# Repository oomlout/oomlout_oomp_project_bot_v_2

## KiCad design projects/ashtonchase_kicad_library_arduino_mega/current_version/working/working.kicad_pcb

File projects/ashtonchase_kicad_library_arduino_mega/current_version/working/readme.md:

# kicad_library
 
## summary 
* id: ashtonchase_kicad_library_arduino_mega
* user: ashtonchase
* name: kicad_library
* board: arduino_mega
* repo: https://github.com/ashtonchase/kicad-library
* src_file_repo_kicad_pcb: template/Arduino_Mega_R3/Arduino_Mega.kicad_pcb
* src_file_repo_kicad_pcb_link: https://github.com/ashtonchase/kicad-library/tree/master/template/Arduino_Mega_R3/Arduino_Mega.kicad_pcb

* src_file_repo_sch: template/Arduino_Mega_R3/Arduino_Mega.sch
* src_file_repo_sch_link: https://github.com/ashtonchase/kicad-library/tree/master/template/Arduino_Mega_R3/Arduino_Mega.sch
* full details link: https://github.com/oomlout/oomlout_oomp_project_bot_v_2/tree/main/projects/ashtonchase_kicad_library_arduino_mega/current_version/working  

## schematic  
  
[schematic (pdf)](working_schematic.pdf) 

## pcb  

[board (pdf)](working.pdf)  

## working_bom
| Id | Designator | Footprint | Quantity | Designation | Supplier and ref |  | None | 
| --- | --- | --- | --- | --- | --- | --- | --- | 
| 1 | P1 | Socket_Strip_Arduino_2x18 | 1 | Digital |  |  | [''] | 
| 2 | P2 | Socket_Strip_Arduino_1x08 | 1 | Power |  |  | [''] | 
| 3 | P3,P4 | Socket_Strip_Arduino_1x08 | 2 | Analog |  |  | [''] | 
| 4 | P5 | Socket_Strip_Arduino_1x10 | 1 | PWM |  |  | [''] | 
| 5 | P6 | Socket_Strip_Arduino_1x08 | 1 | PWM |  |  | [''] | 
| 6 | P7 | Socket_Strip_Arduino_1x08 | 1 | Communication |  |  | [''] | 
| 7 | P8,P9,P10,P11,P12,P13 | Arduino_1pin | 6 | CONN_01X01 |  |  | [''] | 

## bom_schematic
| Ref | Qnty | Value | Cmp name | Footprint | Description | Vendor | DNP | 
| --- | --- | --- | --- | --- | --- | --- | --- | 
| P1 | 1 | Digital | CONN_02X18 | Socket_Arduino_Mega:Socket_Strip_Arduino_2x18 |  |  |  | 
| P2 | 1 | Power | CONN_01X08 | Socket_Arduino_Mega:Socket_Strip_Arduino_1x08 |  |  |  | 
| P3, P4 | 2 | Analog | CONN_01X08 | Socket_Arduino_Mega:Socket_Strip_Arduino_1x08 |  |  |  | 
| P5 | 1 | PWM | CONN_01X10 | Socket_Arduino_Mega:Socket_Strip_Arduino_1x10 |  |  |  | 
| P6 | 1 | PWM | CONN_01X08 | Socket_Arduino_Mega:Socket_Strip_Arduino_1x08 |  |  |  | 
| P7 | 1 | Communication | CONN_01X08 | Socket_Arduino_Mega:Socket_Strip_Arduino_1x08 |  |  |  | 
| P8, P9, P10, P11, P12, P13 | 6 | CONN_01X01 | CONN_01X01 | Socket_Arduino_Mega:Arduino_1pin |  |  |  |

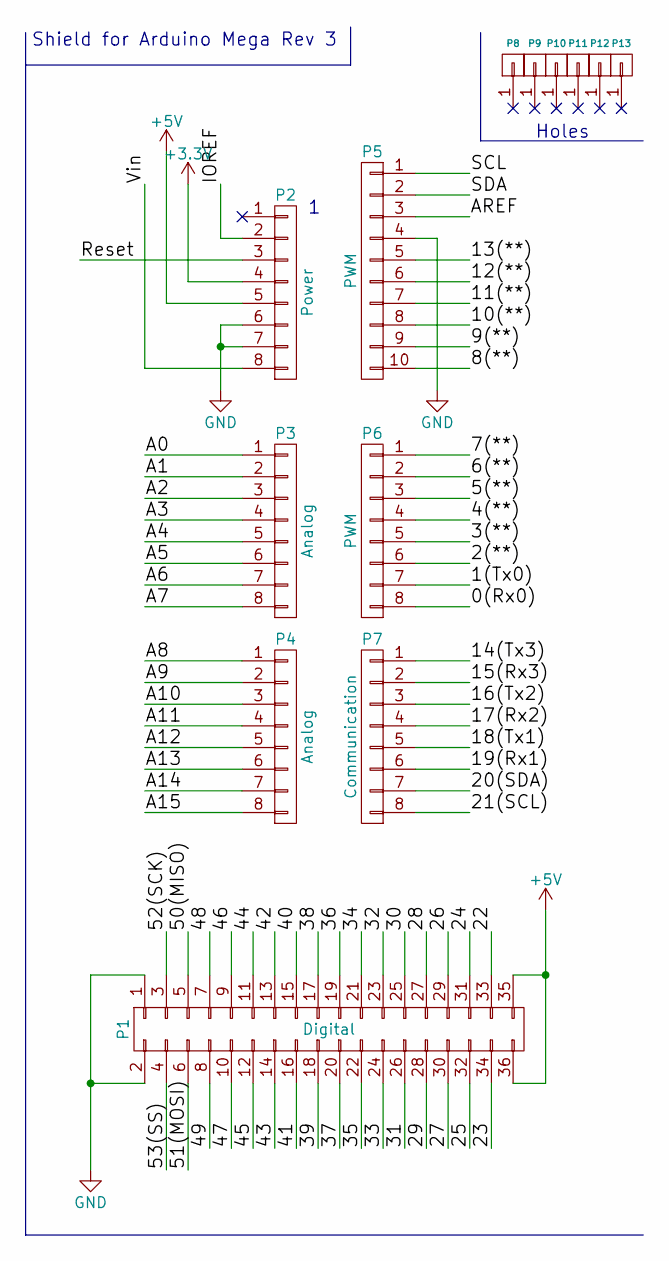
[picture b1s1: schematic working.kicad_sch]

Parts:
P1: Digital; Socket_Strip_Arduino_2x18
P2: Power; Socket_Strip_Arduino_1x08
P3, P4: Analog; Socket_Strip_Arduino_1x08
P5: PWM; Socket_Strip_Arduino_1x10
P6: PWM; Socket_Strip_Arduino_1x08
P7: Communication; Socket_Strip_Arduino_1x08
P8, P9, P10, P11, P12, P13: CONN_01X01; Arduino_1pin

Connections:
+3V3: P2.4
+5V: P1.35, P1.36, P2.5
/0(Rx0): P6.8
/1(Tx0): P6.7
/2(**): P6.6
/3(**): P6.5
/4(**): P6.4
/5(**): P6.3
/6(**): P6.2
/7(**): P6.1
/8(**): P5.10
/9(**): P5.9
/10(**): P5.8
/11(**): P5.7
/12(**): P5.6
/13(**): P5.5
/14(Tx3): P7.1
/15(Rx3): P7.2
/16(Tx2): P7.3
/17(Rx2): P7.4
/18(Tx1): P7.5
/19(Rx1): P7.6
/20(SDA): P7.7
/21(SCL): P7.8
/22: P1.33
/23: P1.34
/24: P1.31
/25: P1.32
/26: P1.29
/27: P1.30
/28: P1.27
/29: P1.28
/30: P1.25
/31: P1.26
/32: P1.23
/33: P1.24
/34: P1.21
/35: P1.22
/36: P1.19
/37: P1.20
/38: P1.17
/39: P1.18
/40: P1.15
/41: P1.16
/42: P1.13
/43: P1.14
/44: P1.11
/45: P1.12
/46: P1.9
/47: P1.10
/48: P1.7
/49: P1.8
/50(MISO): P1.5
/51(MOSI): P1.6
/52(SCK): P1.3
/53(SS): P1.4
/A0: P3.1
/A1: P3.2
/A2: P3.3
/A3: P3.4
/A4: P3.5
/A5: P3.6
/A6: P3.7
/A7: P3.8
/A8: P4.1
/A9: P4.2
/A10: P4.3
/A11: P4.4
/A12: P4.5
/A13: P4.6
/A14: P4.7
/A15: P4.8
/AREF: P5.3
/IOREF: P2.2
/Reset: P2.3
/SCL: P5.1
/SDA: P5.2
/Vin: P2.8
GND: P1.1, P1.2, P2.6, P2.7, P5.4

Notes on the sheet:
Holes
Shield for Arduino Mega Rev 3

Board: 2 copper layers, 13 parts (0 on the bottom side), 2 nets, no tracks yet.

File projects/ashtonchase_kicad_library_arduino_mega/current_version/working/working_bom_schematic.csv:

"Source:","C:\gh\oomlout_oomp_project_bot_v_2\projects\ashtonchase_kicad_library_arduino_mega\current_version\working\working.kicad_sch"
"Date:","25/09/2023 02:56:55"
"Tool:","Eeschema 7.0.6"
"Generator:","C:/Program Files/KiCad/7.0/bin/scripting/plugins/bom_csv_grouped_by_value_with_fp.py"
"Component Count:","13"
"Ref","Qnty","Value","Cmp name","Footprint","Description","Vendor","DNP"
"P1","1","Digital","CONN_02X18","Socket_Arduino_Mega:Socket_Strip_Arduino_2x18","","",""
"P2","1","Power","CONN_01X08","Socket_Arduino_Mega:Socket_Strip_Arduino_1x08","","",""
"P3, P4","2","Analog","CONN_01X08","Socket_Arduino_Mega:Socket_Strip_Arduino_1x08","","",""
"P5","1","PWM","CONN_01X10","Socket_Arduino_Mega:Socket_Strip_Arduino_1x10","","",""
"P6","1","PWM","CONN_01X08","Socket_Arduino_Mega:Socket_Strip_Arduino_1x08","","",""
"P7","1","Communication","CONN_01X08","Socket_Arduino_Mega:Socket_Strip_Arduino_1x08","","",""
"P8, P9, P10, P11, P12, P13","6","CONN_01X01","CONN_01X01","Socket_Arduino_Mega:Arduino_1pin","","",""

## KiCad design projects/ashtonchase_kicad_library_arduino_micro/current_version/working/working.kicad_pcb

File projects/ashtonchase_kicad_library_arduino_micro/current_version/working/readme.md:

# kicad_library
 
## summary 
* id: ashtonchase_kicad_library_arduino_micro
* user: ashtonchase
* name: kicad_library
* board: arduino_micro
* repo: https://github.com/ashtonchase/kicad-library
* src_file_repo_kicad_pcb: template/Arduino_Micro/Arduino_Micro.kicad_pcb
* src_file_repo_kicad_pcb_link: https://github.com/ashtonchase/kicad-library/tree/master/template/Arduino_Micro/Arduino_Micro.kicad_pcb

* src_file_repo_sch: template/Arduino_Micro/Arduino_Micro.sch
* src_file_repo_sch_link: https://github.com/ashtonchase/kicad-library/tree/master/template/Arduino_Micro/Arduino_Micro.sch
* full details link: https://github.com/oomlout/oomlout_oomp_project_bot_v_2/tree/main/projects/ashtonchase_kicad_library_arduino_micro/current_version/working  

## schematic  
  
[schematic (pdf)](working_schematic.pdf) 

## pcb  

[board (pdf)](working.pdf)  

## working_bom
| Id | Designator | Footprint | Quantity | Designation | Supplier and ref |  | None | 
| --- | --- | --- | --- | --- | --- | --- | --- | 
| 1 | P1 | Socket_Strip_Arduino_1x17 | 1 | Digital |  |  | [''] | 
| 2 | P2 | Socket_Strip_Arduino_1x17 | 1 | Analog |  |  | [''] | 
| 3 | P3,P4,P5,P6 | 1pin_Micro | 4 | CONN_01X01 |  |  | [''] | 

## bom_schematic
| Ref | Qnty | Value | Cmp name | Footprint | Description | Vendor | DNP | 
| --- | --- | --- | --- | --- | --- | --- | --- | 
| P1 | 1 | Digital | CONN_01X17 | Socket_Arduino_Micro:Socket_Strip_Arduino_1x17 |  |  |  | 
| P2 | 1 | Analog | CONN_01X17 | Socket_Arduino_Micro:Socket_Strip_Arduino_1x17 |  |  |  | 
| P3, P4, P5, P6 | 4 | CONN_01X01 | CONN_01X01 | Socket_Arduino_Micro:1pin_Micro |  |  |  |

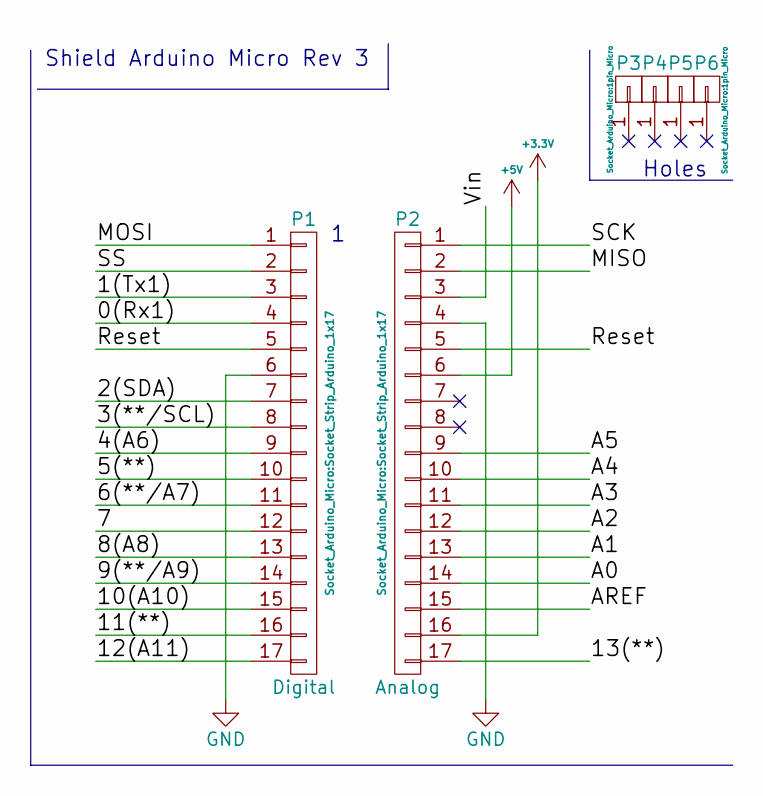
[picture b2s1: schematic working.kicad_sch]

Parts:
P1: Digital; Socket_Strip_Arduino_1x17
P2: Analog; Socket_Strip_Arduino_1x17
P3, P4, P5, P6: CONN_01X01; 1pin_Micro

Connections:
+3V3: P2.16
+5V: P2.6
/0(Rx1): P1.4
/1(Tx1): P1.3
/2(SDA): P1.7
/3(**/SCL): P1.8
/4(A6): P1.9
/5(**): P1.10
/6(**/A7): P1.11
/7: P1.12
/8(A8): P1.13
/9(**/A9): P1.14
/10(A10): P1.15
/11(**): P1.16
/12(A11): P1.17
/13(**): P2.17
/A0: P2.14
/A1: P2.13
/A2: P2.12
/A3: P2.11
/A4: P2.10
/A5: P2.9
/AREF: P2.15
/MISO: P2.2
/MOSI: P1.1
/Reset: P1.5, P2.5
/SCK: P2.1
/SS: P1.2
/Vin: P2.3
GND: P1.6, P2.4

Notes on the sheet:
Shield Arduino Micro Rev 3
Holes

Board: 2 copper layers, 6 parts (0 on the bottom side), 2 nets, no tracks yet.

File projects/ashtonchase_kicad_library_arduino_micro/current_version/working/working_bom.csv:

"Id";"Designator";"Footprint";"Quantity";"Designation";"Supplier and ref";
1;"P1";"Socket_Strip_Arduino_1x17";1;"Digital";;;
2;"P2";"Socket_Strip_Arduino_1x17";1;"Analog";;;
3;"P3,P4,P5,P6";"1pin_Micro";4;"CONN_01X01";;;

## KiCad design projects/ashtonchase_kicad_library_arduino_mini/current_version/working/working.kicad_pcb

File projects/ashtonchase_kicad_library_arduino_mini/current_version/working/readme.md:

# kicad_library
 
## summary 
* id: ashtonchase_kicad_library_arduino_mini
* user: ashtonchase
* name: kicad_library
* board: arduino_mini
* repo: https://github.com/ashtonchase/kicad-library
* src_file_repo_kicad_pcb: template/Arduino_Mini/Arduino_Mini.kicad_pcb
* src_file_repo_kicad_pcb_link: https://github.com/ashtonchase/kicad-library/tree/master/template/Arduino_Mini/Arduino_Mini.kicad_pcb

* src_file_repo_sch: template/Arduino_Mini/Arduino_Mini.sch
* src_file_repo_sch_link: https://github.com/ashtonchase/kicad-library/tree/master/template/Arduino_Mini/Arduino_Mini.sch
* full details link: https://github.com/oomlout/oomlout_oomp_project_bot_v_2/tree/main/projects/ashtonchase_kicad_library_arduino_mini/current_version/working  

## schematic  
  
[schematic (pdf)](working_schematic.pdf) 

## pcb  

[board (pdf)](working.pdf)  

## working_bom
| Id | Designator | Footprint | Quantity | Designation | Supplier and ref |  | None | 
| --- | --- | --- | --- | --- | --- | --- | --- | 
| 1 | P2 | Socket_Strip_Arduino_1x12 | 1 | Digital |  |  | [''] | 
| 2 | P4 | Socket_Strip_Arduino_1x05 | 1 | COM |  |  | [''] | 
| 3 | P5 | Socket_Strip_Arduino_1x12 | 1 | Analog |  |  | [''] | 
| 4 | P1,P3 | Socket_Strip_Arduino_1x02 | 2 | ADC |  |  | [''] | 
| 5 | P6 | Socket_Strip_Arduino_1x02 | 1 | PWR |  |  | [''] | 

## bom_schematic
| Ref | Qnty | Value | Cmp name | Footprint | Description | Vendor | DNP | 
| --- | --- | --- | --- | --- | --- | --- | --- | 
| P1, P3 | 2 | ADC | CONN_01X02 | Socket_Arduino_Mini:Socket_Strip_Arduino_1x02 |  |  |  | 
| P2 | 1 | Digital | CONN_01X12 | Socket_Arduino_Mini:Socket_Strip_Arduino_1x12 |  |  |  | 
| P4 | 1 | COM | CONN_01X05 | Socket_Arduino_Mini:Socket_Strip_Arduino_1x05 |  |  |  | 
| P5 | 1 | Analog | CONN_01X12 | Socket_Arduino_Mini:Socket_Strip_Arduino_1x12 |  |  |  | 
| P6 | 1 | PWR | CONN_01X02 | Socket_Arduino_Mini:Socket_Strip_Arduino_1x02 |  |  |  |

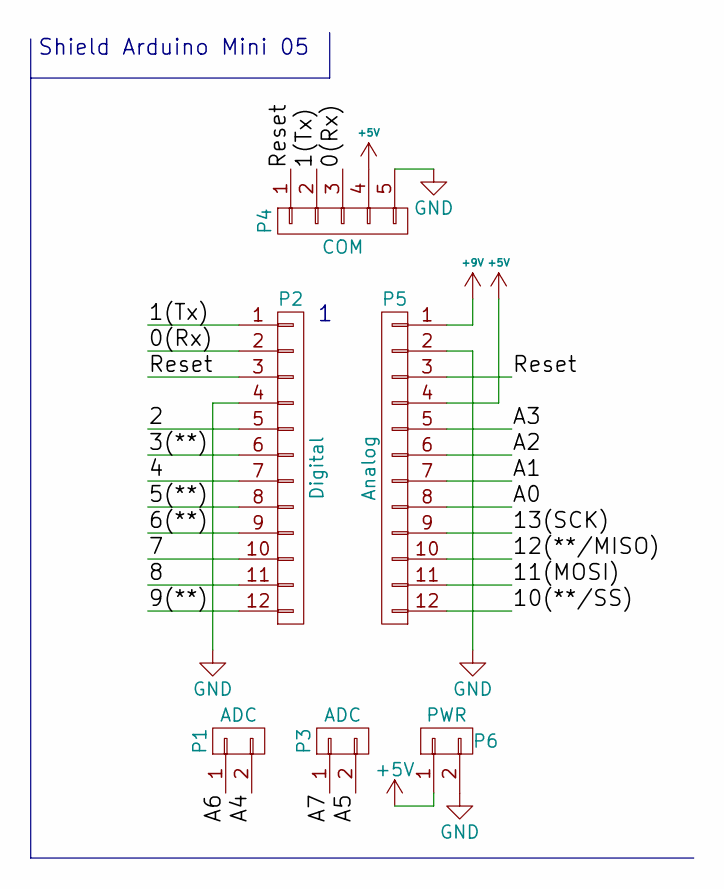
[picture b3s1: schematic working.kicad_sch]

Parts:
P1, P3: ADC; Socket_Strip_Arduino_1x02
P2: Digital; Socket_Strip_Arduino_1x12
P4: COM; Socket_Strip_Arduino_1x05
P5: Analog; Socket_Strip_Arduino_1x12
P6: PWR; Socket_Strip_Arduino_1x02

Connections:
+5V: P4.4, P5.4, P6.1
+9V: P5.1
/0(Rx): P2.2, P4.3
/1(Tx): P2.1, P4.2
/2: P2.5
/3(**): P2.6
/4: P2.7
/5(**): P2.8
/6(**): P2.9
/7: P2.10
/8: P2.11
/9(**): P2.12
/10(**/SS): P5.12
/11(MOSI): P5.11
/12(**/MISO): P5.10
/13(SCK): P5.9
/A0: P5.8
/A1: P5.7
/A2: P5.6
/A3: P5.5
/A4: P1.2
/A5: P3.2
/A6: P1.1
/A7: P3.1
/Reset: P2.3, P4.1, P5.3
GND: P2.4, P4.5, P5.2, P6.2

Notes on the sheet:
Shield Arduino Mini 05

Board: 2 copper layers, 6 parts (0 on the bottom side), 5 nets, no tracks yet.

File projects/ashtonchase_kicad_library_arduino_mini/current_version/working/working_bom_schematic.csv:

"Source:","C:\gh\oomlout_oomp_project_bot_v_2\projects\ashtonchase_kicad_library_arduino_mini\current_version\working\working.kicad_sch"
"Date:","25/09/2023 03:12:44"
"Tool:","Eeschema 7.0.6"
"Generator:","C:/Program Files/KiCad/7.0/bin/scripting/plugins/bom_csv_grouped_by_value_with_fp.py"
"Component Count:","6"
"Ref","Qnty","Value","Cmp name","Footprint","Description","Vendor","DNP"
"P1, P3","2","ADC","CONN_01X02","Socket_Arduino_Mini:Socket_Strip_Arduino_1x02","","",""
"P2","1","Digital","CONN_01X12","Socket_Arduino_Mini:Socket_Strip_Arduino_1x12","","",""
"P4","1","COM","CONN_01X05","Socket_Arduino_Mini:Socket_Strip_Arduino_1x05","","",""
"P5","1","Analog","CONN_01X12","Socket_Arduino_Mini:Socket_Strip_Arduino_1x12","","",""
"P6","1","PWR","CONN_01X02","Socket_Arduino_Mini:Socket_Strip_Arduino_1x02","","",""

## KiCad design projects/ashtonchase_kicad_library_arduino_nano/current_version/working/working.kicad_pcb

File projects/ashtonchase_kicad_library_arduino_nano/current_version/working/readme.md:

# kicad_library
 
## summary 
* id: ashtonchase_kicad_library_arduino_nano
* user: ashtonchase
* name: kicad_library
* board: arduino_nano
* repo: https://github.com/ashtonchase/kicad-library
* src_file_repo_kicad_pcb: template/Arduino_Nano/Arduino_Nano.kicad_pcb
* src_file_repo_kicad_pcb_link: https://github.com/ashtonchase/kicad-library/tree/master/template/Arduino_Nano/Arduino_Nano.kicad_pcb

* src_file_repo_sch: template/Arduino_Nano/Arduino_Nano.sch
* src_file_repo_sch_link: https://github.com/ashtonchase/kicad-library/tree/master/template/Arduino_Nano/Arduino_Nano.sch
* full details link: https://github.com/oomlout/oomlout_oomp_project_bot_v_2/tree/main/projects/ashtonchase_kicad_library_arduino_nano/current_version/working  

## schematic  
  
[schematic (pdf)](working_schematic.pdf) 

## pcb  

[board (pdf)](working.pdf)  

## working_bom
| Id | Designator | Footprint | Quantity | Designation | Supplier and ref |  | None | 
| --- | --- | --- | --- | --- | --- | --- | --- | 
| 1 | P1 | Socket_Strip_Arduino_1x15 | 1 | Digital |  |  | [''] | 
| 2 | P2 | Socket_Strip_Arduino_1x15 | 1 | Analog |  |  | [''] | 
| 3 | P3,P4,P5,P6 | 1pin_Nano | 4 | CONN_01X01 |  |  | [''] | 

## bom_schematic
| Ref | Qnty | Value | Cmp name | Footprint | Description | Vendor | DNP | 
| --- | --- | --- | --- | --- | --- | --- | --- | 
| P1 | 1 | Digital | CONN_01X15 | Socket_Arduino_Nano:Socket_Strip_Arduino_1x15 |  |  |  | 
| P2 | 1 | Analog | CONN_01X15 | Socket_Arduino_Nano:Socket_Strip_Arduino_1x15 |  |  |  | 
| P3, P4, P5, P6 | 4 | CONN_01X01 | CONN_01X01 | Socket_Arduino_Nano:1pin_Nano |  |  |  |

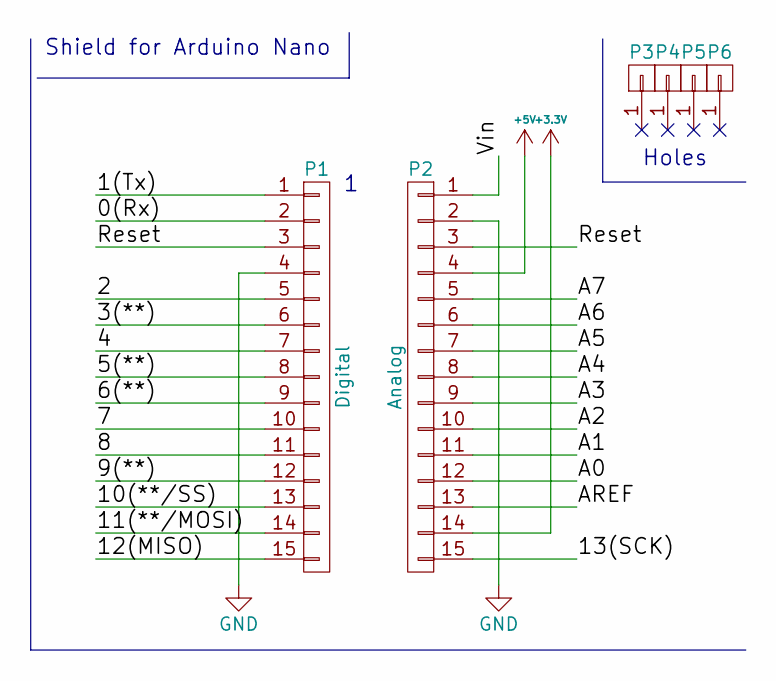
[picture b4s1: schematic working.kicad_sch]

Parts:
P1: Digital; Socket_Strip_Arduino_1x15
P2: Analog; Socket_Strip_Arduino_1x15
P3, P4, P5, P6: CONN_01X01; 1pin_Nano

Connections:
+3V3: P2.14
+5V: P2.4
/0(Rx): P1.2
/1(Tx): P1.1
/2: P1.5
/3(**): P1.6
/4: P1.7
/5(**): P1.8
/6(**): P1.9
/7: P1.10
/8: P1.11
/9(**): P1.12
/10(**/SS): P1.13
/11(**/MOSI): P1.14
/12(MISO): P1.15
/13(SCK): P2.15
/A0: P2.12
/A1: P2.11
/A2: P2.10
/A3: P2.9
/A4: P2.8
/A5: P2.7
/A6: P2.6
/A7: P2.5
/AREF: P2.13
/Reset: P1.3, P2.3
/Vin: P2.1
GND: P1.4, P2.2

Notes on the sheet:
Shield for Arduino Nano
Holes

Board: 2 copper layers, 6 parts (0 on the bottom side), 2 nets, no tracks yet.

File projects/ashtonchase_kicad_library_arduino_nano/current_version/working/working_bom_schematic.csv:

"Source:","C:\gh\oomlout_oomp_project_bot_v_2\projects\ashtonchase_kicad_library_arduino_nano\current_version\working\working.kicad_sch"
"Date:","25/09/2023 03:20:39"
"Tool:","Eeschema 7.0.6"
"Generator:","C:/Program Files/KiCad/7.0/bin/scripting/plugins/bom_csv_grouped_by_value_with_fp.py"
"Component Count:","6"
"Ref","Qnty","Value","Cmp name","Footprint","Description","Vendor","DNP"
"P1","1","Digital","CONN_01X15","Socket_Arduino_Nano:Socket_Strip_Arduino_1x15","","",""
"P2","1","Analog","CONN_01X15","Socket_Arduino_Nano:Socket_Strip_Arduino_1x15","","",""
"P3, P4, P5, P6","4","CONN_01X01","CONN_01X01","Socket_Arduino_Nano:1pin_Nano","","",""

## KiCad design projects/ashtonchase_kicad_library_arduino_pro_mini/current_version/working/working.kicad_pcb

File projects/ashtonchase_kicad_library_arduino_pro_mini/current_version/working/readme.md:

# kicad_library
 
## summary 
* id: ashtonchase_kicad_library_arduino_pro_mini
* user: ashtonchase
* name: kicad_library
* board: arduino_pro_mini
* repo: https://github.com/ashtonchase/kicad-library
* src_file_repo_kicad_pcb: template/Arduino_Pro_Mini/Arduino_Pro_Mini.kicad_pcb
* src_file_repo_kicad_pcb_link: https://github.com/ashtonchase/kicad-library/tree/master/template/Arduino_Pro_Mini/Arduino_Pro_Mini.kicad_pcb

* src_file_repo_sch: template/Arduino_Pro_Mini/Arduino_Pro_Mini.sch
* src_file_repo_sch_link: https://github.com/ashtonchase/kicad-library/tree/master/template/Arduino_Pro_Mini/Arduino_Pro_Mini.sch
* full details link: https://github.com/oomlout/oomlout_oomp_project_bot_v_2/tree/main/projects/ashtonchase_kicad_library_arduino_pro_mini/current_version/working  

## schematic  
  
[schematic (pdf)](working_schematic.pdf) 

## pcb  

[board (pdf)](working.pdf)  

## working_bom
| Id | Designator | Footprint | Quantity | Designation | Supplier and ref |  | None | 
| --- | --- | --- | --- | --- | --- | --- | --- | 
| 1 | P1 | Socket_Strip_Arduino_1x12 | 1 | Digital |  |  | [''] | 
| 2 | P2 | Socket_Strip_Arduino_1x06 | 1 | COM |  |  | [''] | 
| 3 | P3,P5 | Socket_Strip_Arduino_1x02 | 2 | ADC |  |  | [''] | 
| 4 | P4 | Socket_Strip_Arduino_1x12 | 1 | Analog |  |  | [''] | 

## bom_schematic
| Ref | Qnty | Value | Cmp name | Footprint | Description | Vendor | DNP | 
| --- | --- | --- | --- | --- | --- | --- | --- | 
| P1 | 1 | Digital | CONN_01X12 | Socket_Arduino_Pro_Mini:Socket_Strip_Arduino_1x12 |  |  |  | 
| P2 | 1 | COM | CONN_01X06 | Socket_Arduino_Pro_Mini:Socket_Strip_Arduino_1x06 |  |  |  | 
| P3, P5 | 2 | ADC | CONN_01X02 | Socket_Arduino_Pro_Mini:Socket_Strip_Arduino_1x02 |  |  |  | 
| P4 | 1 | Analog | CONN_01X12 | Socket_Arduino_Pro_Mini:Socket_Strip_Arduino_1x12 |  |  |  |

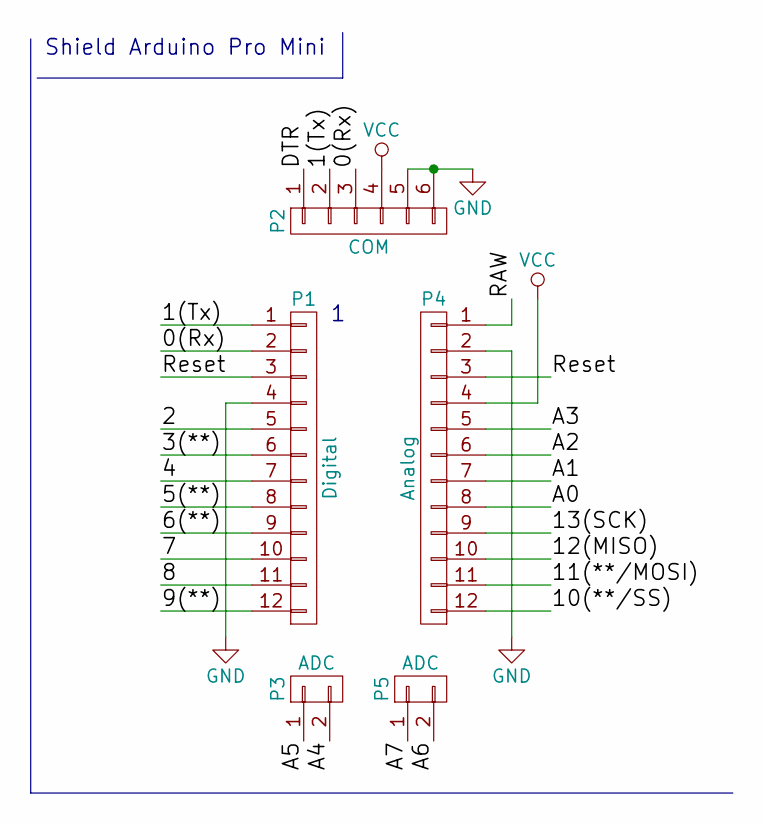
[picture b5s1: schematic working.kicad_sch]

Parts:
P1: Digital; Socket_Strip_Arduino_1x12
P2: COM; Socket_Strip_Arduino_1x06
P3, P5: ADC; Socket_Strip_Arduino_1x02
P4: Analog; Socket_Strip_Arduino_1x12

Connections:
/0(Rx): P1.2, P2.3
/1(Tx): P1.1, P2.2
/2: P1.5
/3(**): P1.6
/4: P1.7
/5(**): P1.8
/6(**): P1.9
/7: P1.10
/8: P1.11
/9(**): P1.12
/10(**/SS): P4.12
/11(**/MOSI): P4.11
/12(MISO): P4.10
/13(SCK): P4.9
/A0: P4.8
/A1: P4.7
/A2: P4.6
/A3: P4.5
/A4: P3.2
/A5: P3.1
/A6: P5.2
/A7: P5.1
/DTR: P2.1
/RAW: P4.1
/Reset: P1.3, P4.3
GND: P1.4, P2.5, P2.6, P4.2
VCC: P2.4, P4.4

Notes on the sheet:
Shield Arduino Pro Mini

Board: 2 copper layers, 5 parts (0 on the bottom side), 5 nets, no tracks yet.

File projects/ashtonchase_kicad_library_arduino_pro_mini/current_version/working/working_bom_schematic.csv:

"Source:","C:\gh\oomlout_oomp_project_bot_v_2\projects\ashtonchase_kicad_library_arduino_pro_mini\current_version\working\working.kicad_sch"
"Date:","25/09/2023 03:28:32"
"Tool:","Eeschema 7.0.6"
"Generator:","C:/Program Files/KiCad/7.0/bin/scripting/plugins/bom_csv_grouped_by_value_with_fp.py"
"Component Count:","5"
"Ref","Qnty","Value","Cmp name","Footprint","Description","Vendor","DNP"
"P1","1","Digital","CONN_01X12","Socket_Arduino_Pro_Mini:Socket_Strip_Arduino_1x12","","",""
"P2","1","COM","CONN_01X06","Socket_Arduino_Pro_Mini:Socket_Strip_Arduino_1x06","","",""
"P3, P5","2","ADC","CONN_01X02","Socket_Arduino_Pro_Mini:Socket_Strip_Arduino_1x02","","",""
"P4","1","Analog","CONN_01X12","Socket_Arduino_Pro_Mini:Socket_Strip_Arduino_1x12","","",""
